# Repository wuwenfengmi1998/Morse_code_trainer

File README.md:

仓库地址 [Github][1]  
备用仓库 [Git.LMVE][2]  
# 莫尔斯电码练习器

## 项目背景
对业余无线电产生了一些兴趣，想学习莫尔斯电码。买一个练习器太贵了，所以打算做一个。

# 开发中
## 硬件&功能
* STM32L03x 32PinIO 48MHz 
* Buzzer 带静音电路
* 3.5 Audio接口 输入与输出 输出电容耦合
* 12864OLED
* EEPROM
* 编码器开关 开机电路
* TYPEC USB 充放电路 带串口芯片
* 电池 电量检测电路

## 软件功能
* 基础UI
* 莫尔斯电码输入识别 手动键与自动键
* 蜂鸣器播放 音频口输出 可静音
* 可设置速率
* 电池电量检测

  [1]: https://github.com/wuwenfengmi1998/Morse_code_trainer
  [2]: https://git.lmve.net/kevin/morse_code_trainer

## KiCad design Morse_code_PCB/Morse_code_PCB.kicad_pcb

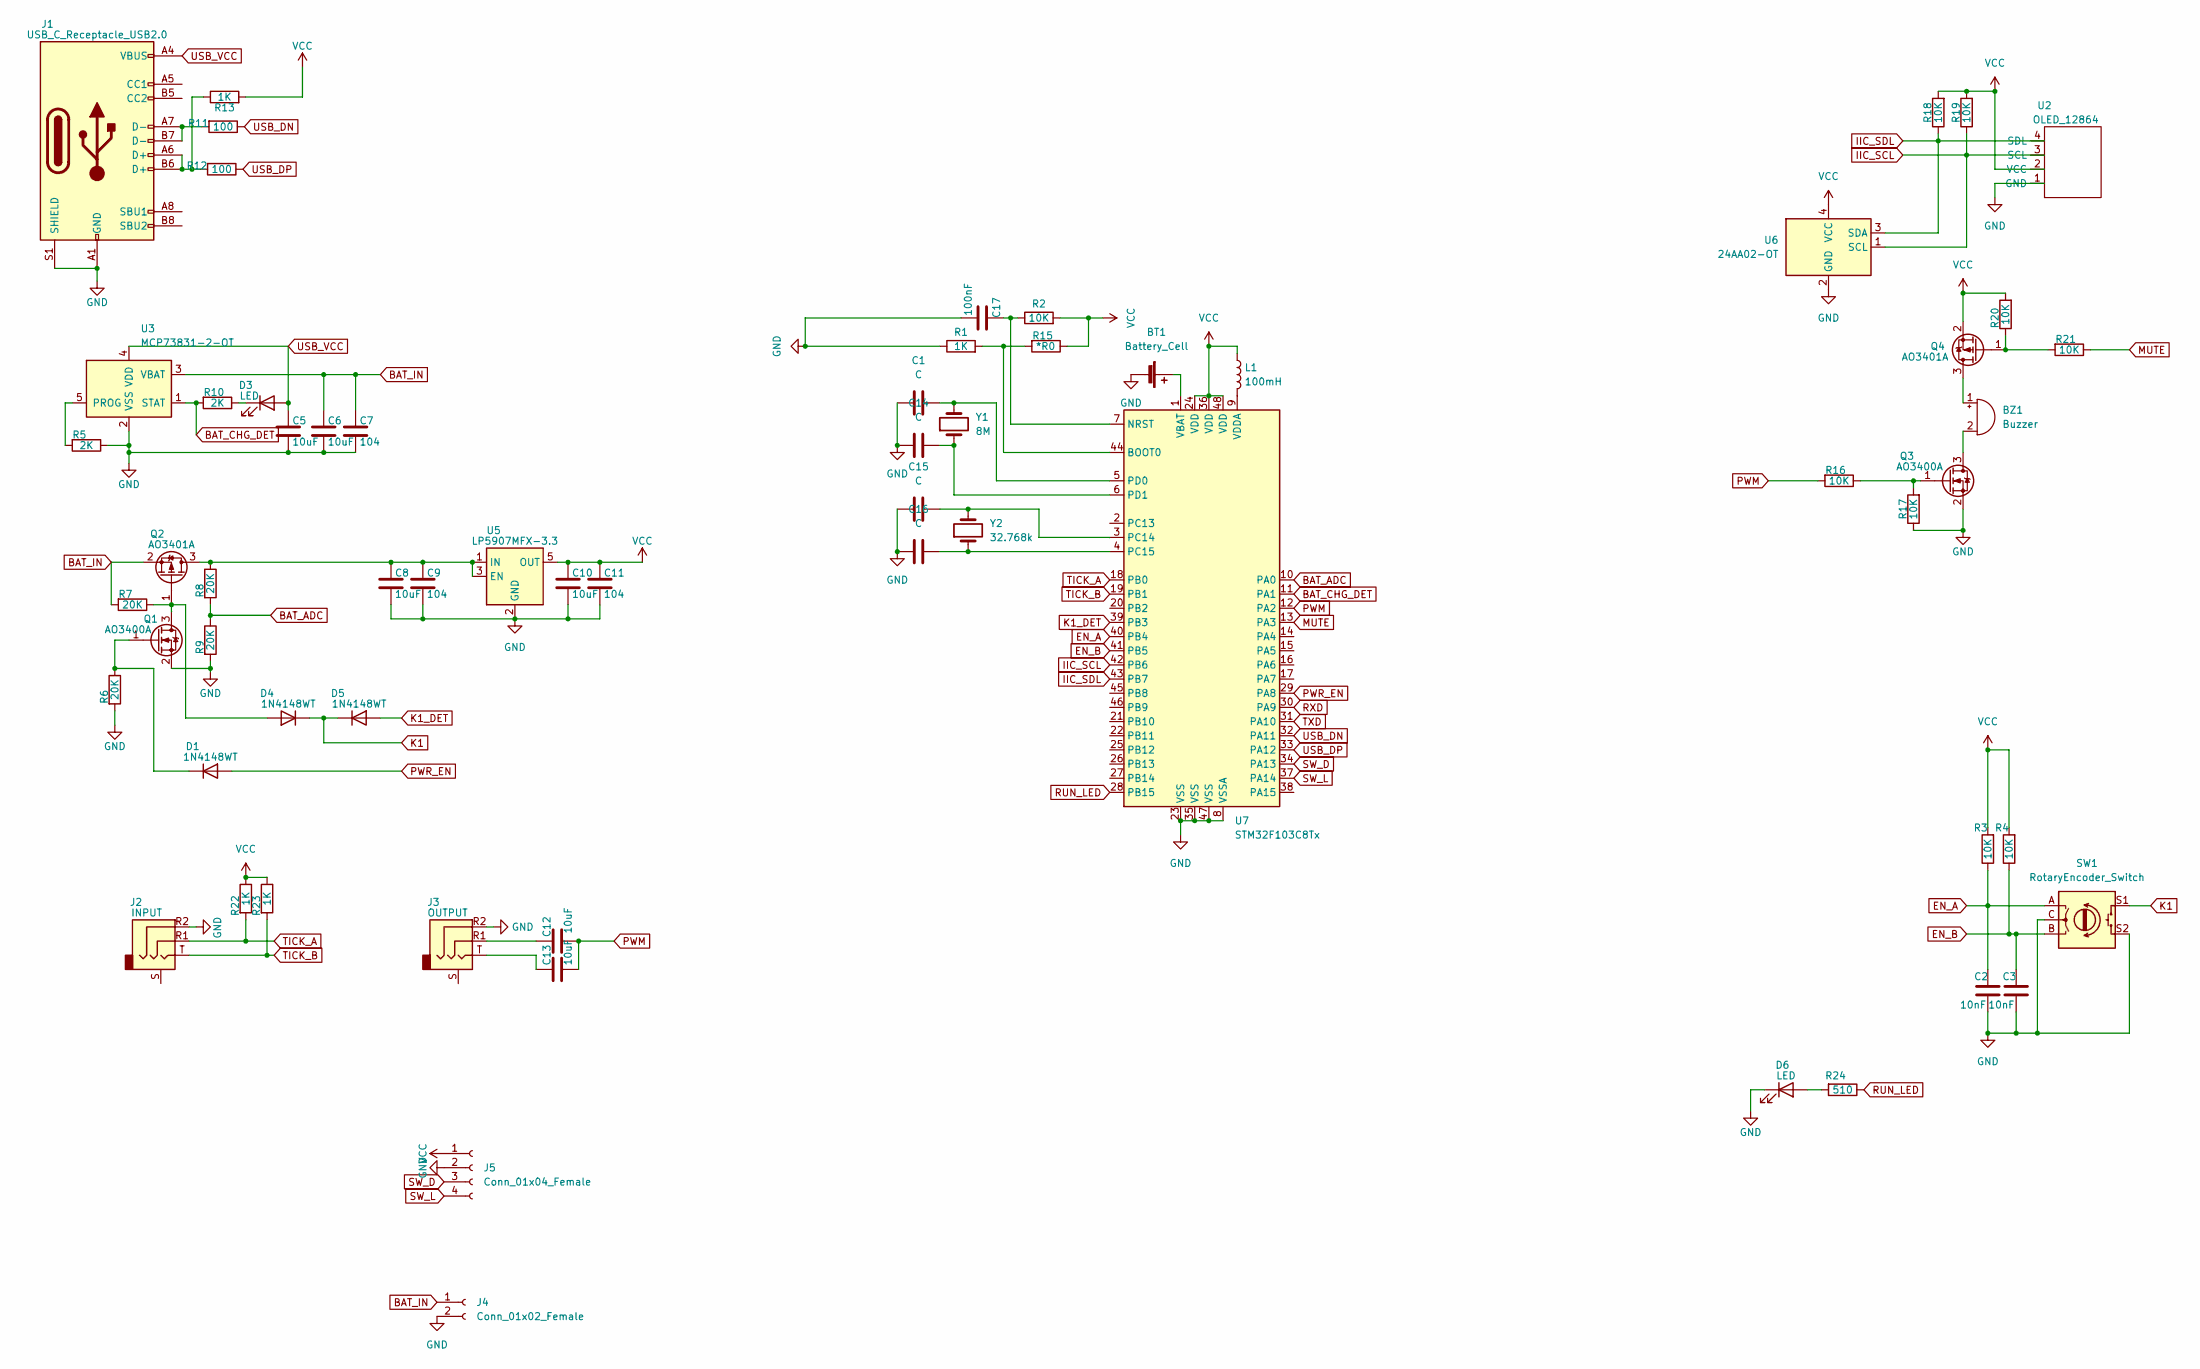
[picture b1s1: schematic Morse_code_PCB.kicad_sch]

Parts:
BT1: Battery_Cell; BAT_BC501SM
BZ1: Buzzer; Buzzer_TDK_PS1240P02BT_D12.2mm_H6.5mm
C1, C14, C15, C16: C; C_0402_1005Metric_Pad0.74x0.62mm_HandSolder
C2, C3: 10nF; C_0603_1608Metric
C5, C6, C8, C10, C12, C13: 10uF; C_1206_3216Metric
C7, C9, C11: 104; C_0805_2012Metric
C17: 100nF; C_0805_2012Metric
D1, D4, D5: 1N4148WT; D_SOD-523
D3, D6: LED; LED_0603_1608Metric
J1: USB_C_Receptacle_USB2.0; USB_C_Receptacle_HRO_TYPE-C-31-M-12
J2: INPUT; Jack_3.5mm_PJ320D_Horizontal
J3: OUTPUT; Jack_3.5mm_PJ320D_Horizontal
J4: Conn_01x02_Female; SIP-2
J5: Conn_01x04_Female; SIP-4
L1: 100mH; L_0805_2012Metric
Q1, Q3: AO3400A; SOT-23
Q2, Q4: AO3401A; SOT-23
R1, R13, R22, R23: 1K; R_0603_1608Metric
R2, R3, R4, R16, R17, R18, R19, R20, R21: 10K; R_0603_1608Metric
R5, R10: 2K; R_0603_1608Metric
R6, R7, R8, R9: 20K; R_0603_1608Metric
R11, R12: 100; R_0603_1608Metric
R15: *R0; R_0402_1005Metric
R24: 510; R_0603_1608Metric
SW1: RotaryEncoder_Switch; EC11
U2: OLED_12864; OLED12864
U3: MCP73831-2-OT; SOT-23-5
U5: LP5907MFX-3.3; SOT-23-5
U6: 24AA02-OT; SOT-23-5
U7: STM32F103C8Tx; LQFP-48_7x7mm_P0.5mm
Y1: 8M; Crystal_SMD_5032-2Pin_5.0x3.2mm
Y2: 32.768k; Crystal_SMD_3215-2Pin_3.2x1.5mm

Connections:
BAT_ADC: R8.2, R9.1, U7.10 (PA0)
BAT_CHG_DET: R10.2, U3.1 (STAT), U7.11 (PA1)
BAT_IN: C6.1, C7.1, J4.1, Q2.2 (S), R7.2, U3.3 (VBAT)
EN_A: C2.1, R3.1, SW1.A, U7.40 (PB4)
EN_B: C3.1, R4.1, SW1.B, U7.41 (PB5)
GND: BT1.2 (-), C1.1, C2.2, C3.2, C5.2, C6.2, C7.2, C8.2, C9.2, C10.2, C11.2, C14.1, C15.1, C16.1, C17.2, D6.1 (K), J1.A1 (GND), J1.A12 (GND), J1.B1 (GND), J1.B12 (GND), J1.S1 (SHIELD), J2.R2, J3.R2, J4.2, J5.2, Q1.2 (S), Q3.2 (S), R1.1, R5.1, R6.2, R9.2, R17.1, SW1.C, SW1.S2, U2.1 (GND), U3.2 (VSS), U5.2 (GND), U6.2 (GND), U7.8 (VSSA), U7.23 (VSS), U7.35 (VSS), U7.47 (VSS)
IIC_SCL: R19.1, U2.3 (SCL), U6.1 (SCL), U7.42 (PB6)
IIC_SDL: R18.1, U2.4 (SDL), U6.3 (SDA), U7.43 (PB7)
K1: D4.1 (K), D5.1 (K), SW1.S1
K1_DET: D5.2 (A), U7.39 (PB3)
MUTE: R21.1, U7.13 (PA3)
unnamed: BT1.1 (+), U7.1 (VBAT)
unnamed: BZ1.1 (-), Q4.3 (D)
unnamed: BZ1.2 (+), Q3.3 (D)
unnamed: C8.1, C9.1, Q2.3 (D), R8.1, U5.1 (IN), U5.3 (EN)
unnamed: C12.1, J3.R1
unnamed: C13.1, J3.T
unnamed: D1.1 (K), Q1.1 (G), R6.1
unnamed: D3.1 (K), R10.1
unnamed: D4.2 (A), Q1.3 (D), Q2.1 (G), R7.1
unnamed: D6.2 (A), R24.2
unnamed: Q3.1 (G), R16.1, R17.2
unnamed: Q4.1 (G), R20.1, R21.2
unnamed: R5.2, U3.5 (PROG)
unnamed: J1.A7 (D-), J1.B7 (D-), R11.2
unnamed: J1.A6 (D+), J1.B6 (D+), R12.2, R13.1
unnamed: C15.2, U7.3 (PC14), Y2.2
unnamed: C16.2, U7.4 (PC15), Y2.1
unnamed: C1.2, U7.5 (PD0), Y1.2
unnamed: C14.2, U7.6 (PD1), Y1.1
unnamed: C17.1, R2.1, U7.7 (NRST)
unnamed: L1.2, U7.9 (VDDA)
unnamed: R1.2, R15.2, U7.44 (BOOT0)
PWM: C12.2, C13.2, R16.2, U7.12 (PA2)
PWR_EN: D1.2 (A), U7.29 (PA8)
RUN_LED: R24.1, U7.28 (PB15)
RXD: U7.30 (PA9)
SW_D: J5.3, U7.34 (PA13)
SW_L: J5.4, U7.37 (PA14)
TICK_A: J2.R1, R22.2, U7.18 (PB0)
TICK_B: J2.T, R23.2, U7.19 (PB1)
TXD: U7.31 (PA10)
USB_DN: R11.1, U7.32 (PA11)
USB_DP: R12.1, U7.33 (PA12)
USB_VCC: C5.1, D3.2 (A), J1.A4 (VBUS), J1.A9 (VBUS), J1.B4 (VBUS), J1.B9 (VBUS), U3.4 (VDD)
VCC: C10.1, C11.1, J5.1, L1.1, Q4.2 (S), R2.2, R3.2, R4.2, R13.2, R15.1, R18.2, R19.2, R20.2, R22.1, R23.1, U2.2 (VCC), U5.5 (OUT), U6.4 (VCC), U7.24 (VDD), U7.36 (VDD), U7.48 (VDD)

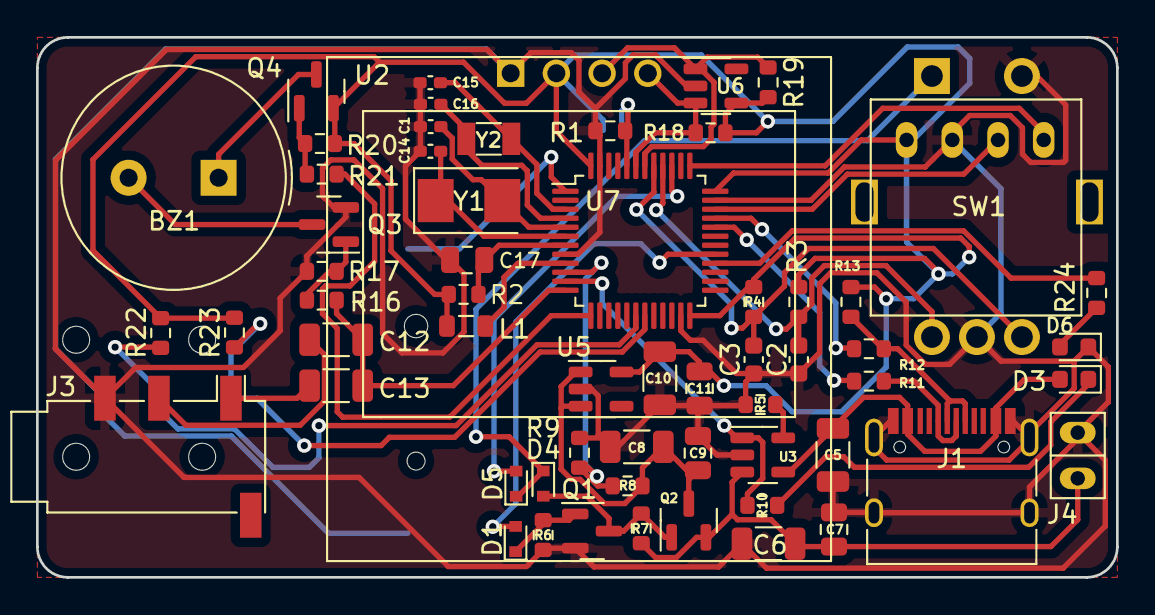
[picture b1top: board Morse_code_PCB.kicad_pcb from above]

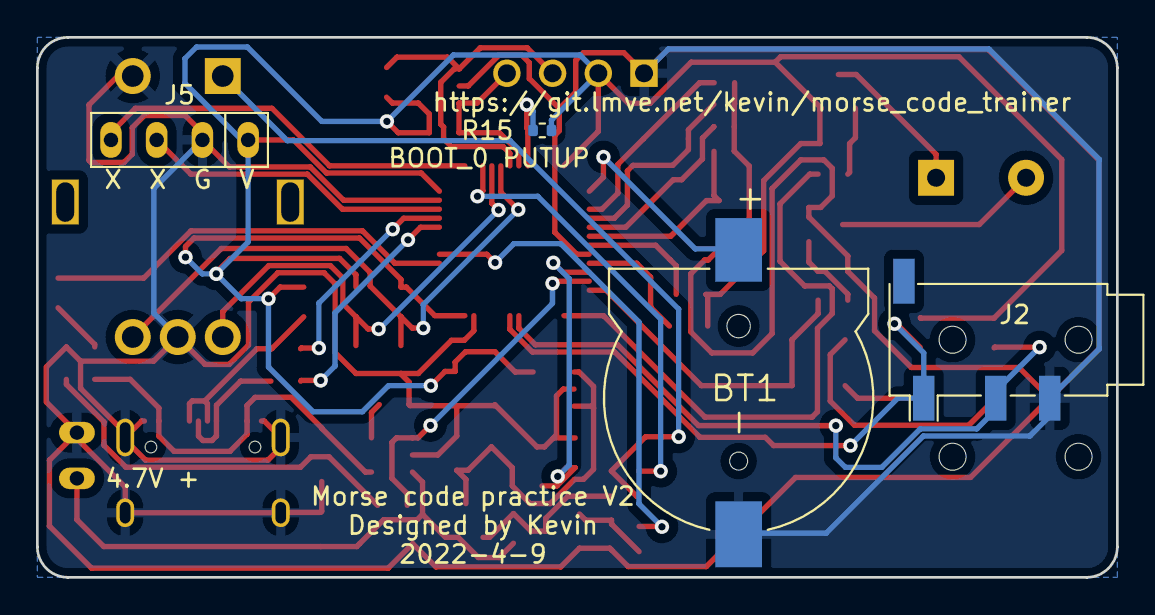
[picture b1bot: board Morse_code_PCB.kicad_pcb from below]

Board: 2 copper layers, 60.0 x 30.0 mm, 64 parts (4 on the bottom side), 44 nets.

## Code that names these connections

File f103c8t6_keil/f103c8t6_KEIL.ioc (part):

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Mcu.Name=STM32F103C(8-B)Tx
Mcu.Package=LQFP48
Mcu.UserName=STM32F103C8Tx
PA13.Mode=Serial_Wire
PA13.Signal=SYS_JTMS-SWDIO
PA14.Mode=Serial_Wire
PA14.Signal=SYS_JTCK-SWCLK
PA2.Signal=S_TIM2_CH3
PA3.GPIOParameters=GPIO_Speed,PinState,GPIO_PuPd,GPIO_Label,GPIO_ModeDefaultOutputPP
PA3.GPIO_Label=mute
PA3.GPIO_ModeDefaultOutputPP=GPIO_MODE_OUTPUT_PP
PA3.GPIO_PuPd=GPIO_PULLUP
PA3.GPIO_Speed=GPIO_SPEED_FREQ_HIGH
PA3.PinState=GPIO_PIN_SET
PA3.Signal=GPIO_Output
PA8.GPIOParameters=GPIO_Speed,GPIO_PuPd,GPIO_Label
PA8.GPIO_Label=pwr_en
PA8.GPIO_PuPd=GPIO_PULLDOWN
PA8.GPIO_Speed=GPIO_SPEED_FREQ_HIGH
PA8.Signal=GPIO_Output
PB0.GPIOParameters=GPIO_PuPd,GPIO_Label,GPIO_ModeDefaultEXTI
PB0.GPIO_Label=tack_a
PB0.GPIO_ModeDefaultEXTI=GPIO_MODE_IT_RISING_FALLING
PB0.GPIO_PuPd=GPIO_PULLUP
PB0.Signal=GPXTI0
PB1.GPIOParameters=GPIO_PuPd,GPIO_Label,GPIO_ModeDefaultEXTI
PB1.GPIO_Label=tack_b
PB1.GPIO_ModeDefaultEXTI=GPIO_MODE_IT_RISING_FALLING
PB1.GPIO_PuPd=GPIO_PULLUP
PB1.Signal=GPXTI1
PB12.GPIOParameters=GPIO_Speed,PinState,GPIO_PuPd,GPIO_Label,GPIO_ModeDefaultOutputPP
PB12.GPIO_Label=run_led2
PB12.GPIO_ModeDefaultOutputPP=GPIO_MODE_OUTPUT_PP
PB12.GPIO_PuPd=GPIO_NOPULL
PB12.GPIO_Speed=GPIO_SPEED_FREQ_LOW
PB12.PinState=GPIO_PIN_RESET
PB12.Signal=GPIO_Output
PB15.GPIOParameters=GPIO_Speed,PinState,GPIO_PuPd,GPIO_Label
PB15.GPIO_Label=run_led
PB15.GPIO_PuPd=GPIO_PULLUP
PB15.GPIO_Speed=GPIO_SPEED_FREQ_HIGH
PB15.PinState=GPIO_PIN_SET
PB15.Signal=GPIO_Output
PB3.GPIOParameters=GPIO_PuPd,GPIO_Label,GPIO_ModeDefaultEXTI
PB3.GPIO_Label=en_c
PB3.GPIO_ModeDefaultEXTI=GPIO_MODE_IT_RISING_FALLING
PB3.GPIO_PuPd=GPIO_PULLUP
PB3.Signal=GPXTI3
PB4.GPIOParameters=GPIO_PuPd,GPIO_Label,GPIO_ModeDefaultEXTI
PB4.GPIO_Label=en_a
PB4.GPIO_ModeDefaultEXTI=GPIO_MODE_IT_RISING
PB4.GPIO_PuPd=GPIO_PULLUP
PB4.Signal=GPXTI4
PB5.GPIOParameters=GPIO_PuPd,GPIO_Label
PB5.GPIO_Label=en_b
PB5.GPIO_PuPd=GPIO_PULLUP
PB5.Signal=GPIO_Input
PB6.Mode=I2C
PB6.Signal=I2C1_SCL
PB7.Mode=I2C
PB7.Signal=I2C1_SDA
PC14-OSC32_IN.Mode=LSE-External-Oscillator
PC14-OSC32_IN.Signal=RCC_OSC32_IN
PC15-OSC32_OUT.Mode=LSE-External-Oscillator
PC15-OSC32_OUT.Signal=RCC_OSC32_OUT
PD0-OSC_IN.Mode=HSE-External-Oscillator
PD0-OSC_IN.Signal=RCC_OSC_IN
PD1-OSC_OUT.Mode=HSE-External-Oscillator
PD1-OSC_OUT.Signal=RCC_OSC_OUT
RCC.SYSCLKFreq_VALUE=72000000
RCC.SYSCLKSource=RCC_SYSCLKSOURCE_PLLCLK
board=custom

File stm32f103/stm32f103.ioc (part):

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Mcu.Name=STM32F103C(8-B)Tx
Mcu.Package=LQFP48
Mcu.UserName=STM32F103C8Tx
PA0-WKUP.Signal=ADCx_IN0
PA1.Signal=GPIO_Input
PA10.Mode=Asynchronous
PA10.Signal=USART1_RX
PA11.Mode=Device
PA11.Signal=USB_DM
PA12.Mode=Device
PA12.Signal=USB_DP
PA13.Mode=Serial_Wire
PA13.Signal=SYS_JTMS-SWDIO
PA14.Mode=Serial_Wire
PA14.Signal=SYS_JTCK-SWCLK
PA9.Mode=Asynchronous
PA9.Signal=USART1_TX
PB6.Mode=I2C
PB6.Signal=I2C1_SCL
PB7.Mode=I2C
PB7.Signal=I2C1_SDA
PC14-OSC32_IN.Mode=LSE-External-Oscillator
PC14-OSC32_IN.Signal=RCC_OSC32_IN
PC15-OSC32_OUT.Mode=LSE-External-Oscillator
PC15-OSC32_OUT.Signal=RCC_OSC32_OUT
PD0-OSC_IN.Mode=HSE-External-Oscillator
PD0-OSC_IN.Signal=RCC_OSC_IN
PD1-OSC_OUT.Mode=HSE-External-Oscillator
PD1-OSC_OUT.Signal=RCC_OSC_OUT
RCC.SYSCLKFreq_VALUE=72000000
RCC.SYSCLKSource=RCC_SYSCLKSOURCE_PLLCLK
board=custom

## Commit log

2022-03-14 新建工程 Signed-off-by: kevin <kevin@lmve.net>
2022-03-14 画了一点PCB Signed-off-by: kevin <kevin@lmve.net>
2022-03-15 updata PCB Signed-off-by: kevin <kevin@lmve.net>
2022-03-15 输入引脚 Signed-off-by: kevin <kevin@lmve.net>
2022-03-15 屏蔽一些内容 Signed-off-by: kevin <kevin@lmve.net>
2022-03-15 画了个12864OLED封装 Signed-off-by: kevin <kevin@lmve.net>
2022-03-16 摸鱼画了一点 Signed-off-by: kevin <kevin@lmve.net>
2022-03-16 updata Signed-off-by: kevin <kevin@lmve.net>
2022-03-16 updata PCB
2022-03-17 Create LICENSE
2022-03-17 又是12点了，下班后累的不想动，随便折腾一会又该睡觉了 明天摸鱼画吧
    画好了电源部分。。
2022-03-18 PCB画完 Signed-off-by: kevin <kevin@lmve.net>
2022-03-18 step Signed-off-by: kevin <kevin@lmve.net>
2022-03-18 打板测试 Signed-off-by: kevin <kevin@lmve.net>
2022-03-18 UPDATA README Signed-off-by: kevin <kevin@lmve.net>
2022-03-25 部分焊接完成，开始调试程序 Signed-off-by: kevin <kevin@lmve.net>
2022-03-27 OLED驱动 RAM AND FLASH不是很够，只能直接读写屏幕 Signed-off-by: kevin <kevin@lmve.net>
2022-03-27 显示字符串 Signed-off-by: kevin <kevin@lmve.net>
2022-03-28 获取引脚信号 Signed-off-by: kevin <kevin@lmve.net>
2022-03-28 解码 Signed-off-by: kevin <kevin@lmve.net>
2022-03-28 上拉引脚 Signed-off-by: kevin <kevin@lmve.net>
2022-04-02 内存写满了
2022-04-02 PCB0.5版 Signed-off-by: kevin <kevin@lmve.net>
2022-04-02 PCB updata Signed-off-by: kevin <kevin@lmve.net>
2022-04-08 updata
2022-04-15 new code project Signed-off-by: kevin <kevin@lmve.net>
2022-04-15 同时安装keil和cubeide后cubeide编译出来的玩意一直无法运行。被迫用keil开发 Signed-off-by: kevin <kevin@lmve.net>
2022-04-15 OLED 驱动 Signed-off-by: kevin <kevin@lmve.net>
2022-04-16 绘图函数 Signed-off-by: kevin <kevin@lmve.net>
2022-04-16 屏幕加速显示，静态大概有100帧，动态显示随机数大概30帧 Signed-off-by: kevin <kevin@lmve.net>
2022-04-16 基本功能移植 Signed-off-by: kevin <kevin@lmve.net>
2022-04-28 ENCODE Signed-off-by: kevin <kevin@lmve.net>
2022-04-28 编码器驱动 菜单功能 Signed-off-by: kevin <kevin@lmve.net>
2022-05-01 输入方式改成中断，开启了两个定时器 Signed-off-by: kevin <kevin@lmve.net>
2022-05-01 按钮中断触发 Signed-off-by: kevin <kevin@lmve.net>
2022-05-02 实现功能 但似乎可以不用中断实现 Signed-off-by: kevin <kevin@lmve.net>
2022-05-05 优化按钮消息循环,同时将按钮改为下降沿触发 Signed-off-by: kevin <kevin@lmve.net>
2022-05-05 优化输入 Signed-off-by: kevin <kevin@lmve.net>
2022-05-05 加一些常量 Signed-off-by: kevin <kevin@lmve.net>
